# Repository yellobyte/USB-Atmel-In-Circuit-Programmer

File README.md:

# USB Atmel in-circuit programmer for AVR controllers #

This is yet another version of Thomas Fischl's [USBasp](https://www.fischl.de/usbasp/) device, an USB in-circuit programmer for Atmel AVR controllers.

The idea to put the USBasp into a nice little enclosure from [Fischer Elektronik](https://www.fischerelektronik.de) (Enclosure Model: FR 55 25 80 ME) I got from [Ulrich Radig's](https://www.ulrichradig.de/home/index.php/avr/usb-avr-prog) website.

What I really missed were some buttons to quickly select/deselect the two very helpful features "Slow Programming Speed" and "Powering Target" if needed. Further I missed a small 6-pin box header with 1.27mm pitch for connections to small targets that don't have enough space on their PCB to fit a big 10-pin/6-pin box header with 2.54mm pitch (20.3mm x 8.9mm resp. 15.22mm x 8.9mm in size).

Therefore I integrated those little goodies and that's the result as shown below.

### Front side with 2 Buttons and USB Socket: ###

### Rear side with box headers (1.27mm/2.54mm pitch) and LEDs: ###

### Flashing a target via small box header: ###

## Some technical infos ##

The PCB is very similar to the one Ulrich Radig created for the same enclosure. As mentioned before, I additionally added 2 subminiature push buttons and a small Samtec 6-pin box header with 1.27mm pitch.

Wiring of both headers (6-pin & 10-pin) follow the standards for AVR in-system programming. If you are interested and want to dive into detail, have a look at paragraph "In-System Programming interface" [here](https://www.ladyada.net/learn/avr/programming.html).

The software on the Atmega8 is original USBasp code from Thomas Fischl.

Button S2 is for powering the target. The 5V power supply to the target is fused with a 0.2A self recovering fuse. If the target needs more current it must be powered seperately.

Button S1 is for selecting a slow target programming speed. This is very helpful if one tries to flash new AVR controller chips for the very first time. Some AVR controllers, when delivered, use by default an internal clock generator running on a low frequency and therefore won't answer when addressed by an USBasp with normal programming speed, because it is simply too fast for them. That can be a real trap for AVR novices...

Jumper JP1 is only (temporarily) shorted when the Atmega8 in the programmer must be programmed itself. It should be open by default.

The little spring (shown in the lower left corner in the picture above) connects the USB socket shield properly with the aluminium enclosure. The enclosure itself (and therefore the USB cable shield) is only connected to GND of the circuitry via R7||C5 ! 

The 2 subminiature push buttons (Manufacturer "NKK Switches", Model "BB16AH-FA") and the little box header with 1.27mm pitch (Manufacturer Samtec, Model "SHF-103-01-L-D-TH") are normally available from Mouser/Farnell/etc.

## PCB Files ##

You find the schematic, board pictures and the Gerber production files (rev 1.1) in folder [**PCB**](https://github.com/yellobyte/USB-Atmel-In-Circuit-Programmer/blob/main/PCB). I zipped all necessary Gerber files into file "USBasp Gerber Files Rev1.1.zip".  

All you need is to send the zip file to a decent PCB manufacturer, pay and wait for the PCB(s) to arrive at your doorstep.

Remark:  
The pictures in folder [**Doc**](https://github.com/yellobyte/USB-Atmel-In-Circuit-Programmer/blob/main/Doc) still show board revision 1.0.  Revision 1.1 is almost identical and contains only cosmetic changes.

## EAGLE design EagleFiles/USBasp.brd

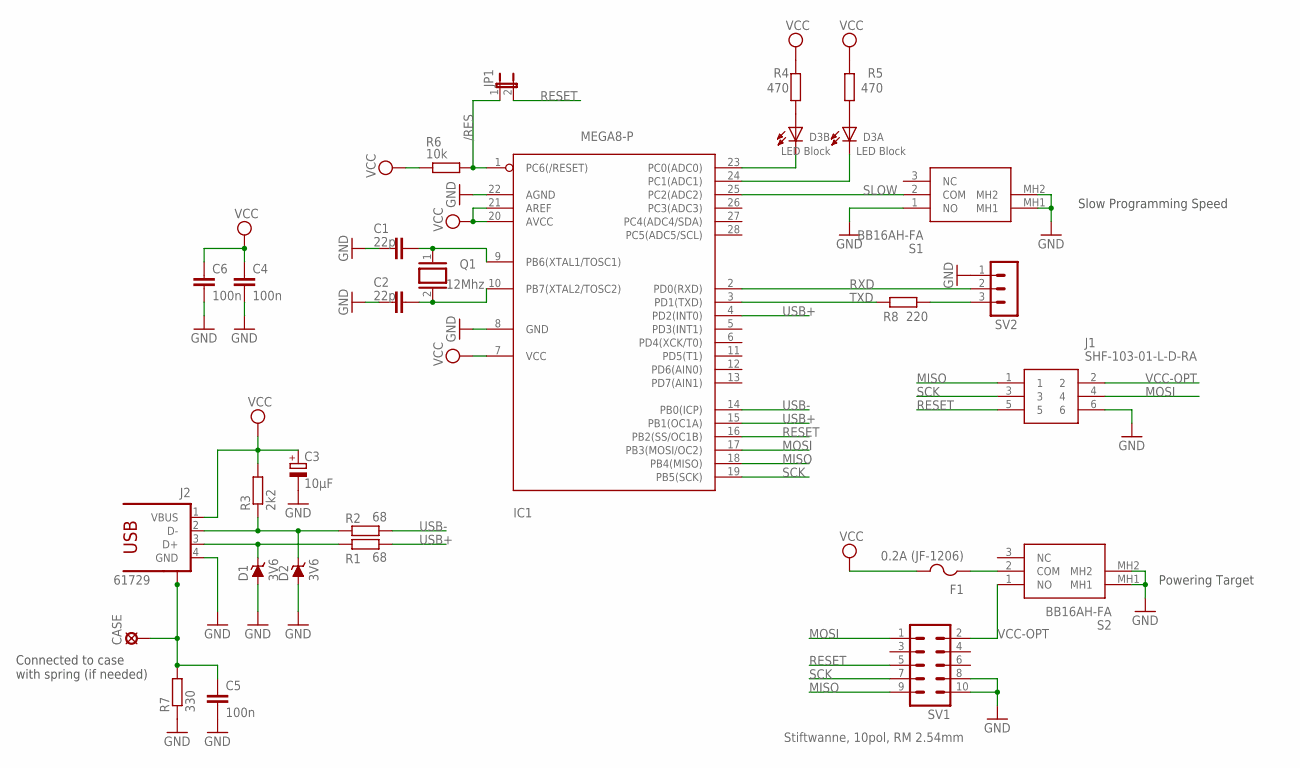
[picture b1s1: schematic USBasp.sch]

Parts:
C1, C2: 22p; C025-024X044
C3: 10µF; E2,5-6
C4, C5, C6: 100n; C050-024X044
CASE: LSP10
D1, D2: 3V6; DO35Z10
D3: LED Block; 1801_PINS_SWAPPED
F1: 0.2A (JF-1206); R1206
IC1: MEGA8-P; DIL28-3
J1: SHF-103-01-L-D-RA; SHF10301LDRA
J2: 61729
JP1: JP1E; JP1
Q1: 12Mhz; QS
R1, R2: 68; 0207/10
R3: 2k2; 0207/10
R4, R5: 470; 0207/10
R6: 10k; 0207/10
R7: 330; 0207/10
R8: 220; R0805
S1, S2: BB16AH-FA; BB16AHFA
SV1: Stiftwanne, 10pol, RM 2.54mm; ML10L
SV2: MA03-1

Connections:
/RES: IC1.1 (PC6(/RESET)), JP1.1, R6.2
GND: C1.1, C2.1, C3.-, C4.2, C5.2, C6.2, D1.A, D2.A, IC1.8 (GND), IC1.22 (AGND), J1.6, J2.4 (GND), R7.1, S1.1 (NO), S1.MH1, S1.MH2, S2.MH1, S2.MH2, SV1.8, SV1.10, SV2.1
MISO: IC1.18 (PB4(MISO)), J1.1, SV1.9
MOSI: IC1.17 (PB3(MOSI/OC2)), J1.4, SV1.1
unnamed: D3.A1 (A), R4.1
unnamed: C5.1, CASE.MP, J2.S1, J2.S2, R7.2
unnamed: C1.2, IC1.9 (PB6(XTAL1/TOSC1)), Q1.1
unnamed: C2.2, IC1.10 (PB7(XTAL2/TOSC2)), Q1.2
unnamed: D1.C, J2.3 (D+), R1.1
unnamed: D2.C, J2.2 (D-), R2.1, R3.1
unnamed: D3.A, R5.1
unnamed: D3.K1 (K), IC1.23 (PC0(ADC0))
unnamed: D3.K, IC1.24 (PC1(ADC1))
unnamed: F1.1, S2.2 (COM)
unnamed: R8.2, SV2.3
RESET: IC1.16 (PB2(SS/OC1B)), J1.5, JP1.2, SV1.5
RXD: IC1.2 (PD0(RXD)), SV2.2
SCK: IC1.19 (PB5(SCK)), J1.3, SV1.7
SLOW: IC1.25 (PC2(ADC2)), S1.2 (COM)
TXD: IC1.3 (PD1(TXD)), R8.1
USB+: IC1.4 (PD2(INT0)), IC1.15 (PB1(OC1A)), R1.2
USB-: IC1.14 (PB0(ICP)), R2.2
VCC: C3.+, C4.1, C6.1, F1.2, IC1.7 (VCC), IC1.20 (AVCC), IC1.21 (AREF), J2.1 (VBUS), R3.2, R4.2, R5.2, R6.1
VCC-OPT: J1.2, S2.1 (NO), SV1.2

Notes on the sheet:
Powering Target
Slow Programming Speed
Connected to case with spring (if needed)

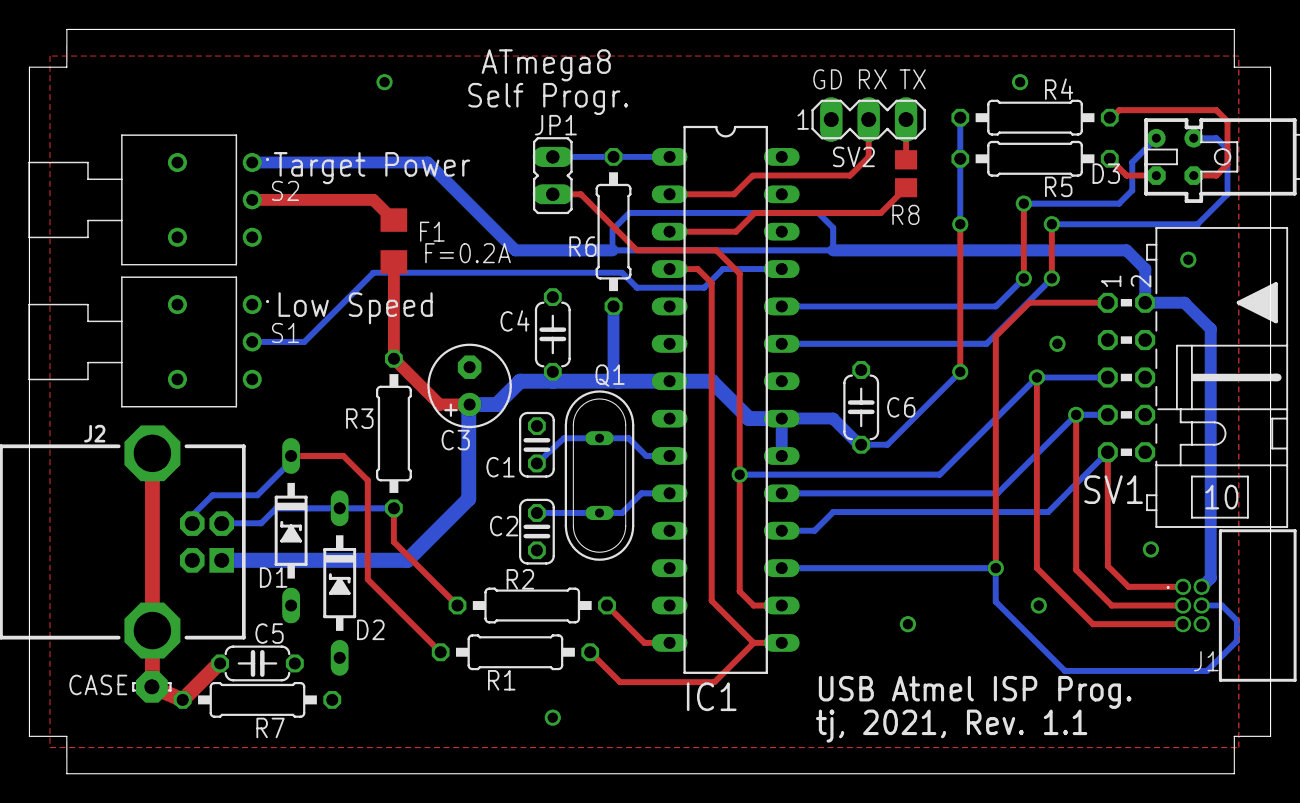
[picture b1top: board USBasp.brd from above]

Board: 2 copper layers, 84.3 x 50.6 mm, 28 parts (0 on the bottom side), 24 nets.

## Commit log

2021-07-07 Pic resolution optimized
2021-07-07 Readme updated
2025-04-27 Update USBasp-BOM.zip
    USBasp-BOM.csv added to USBasp-BOM.zip

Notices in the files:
parts and their libraries:
con-usb: Copyright (C) 2008, Bob Starr
